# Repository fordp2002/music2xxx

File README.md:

# music2xxx
## Hybrid Music 2000 Clone Midi I/O PCB

This is a hardware clone of the Hybrid Music 2000 Midi add-on for the Acorn BBC Microcomputer model B and Master 128 designed for use with the Hybrid Music 5000 system. It is designed to stack on the Music5xxx clone PCB, and uses the 5V supply from the main board. If used independently of the Music5xxx, you will need to provide a 5V supply - this can come from the BBC Micro's auxiliary power connector.

The Music 2000 Midi interface combined with the AMPLE programming language and the Hybrid Studio 5000 Studio software provides versatile control of external Midi devices. The Music 2000 has 3 Midi output sockets.

Despite having an on-board Midi input port, AMPLE and the Hybrid System cannot use it directly. It is assumed that the Hybrid system is used as a controller and sequencer. However, it is possible to address the interface from user programs.

## The clone

It is designed in Kicad, based upon Colin Fraser's reverse-engineered schematic. http://www.colinfraser.com/m5000/m2000sch.pdf This version uses a different opto-isolator on the Midi input, and implements activity LEDs for the Midi outputs. 

Currently all the 74xx series logic ICs are available new. The 6850 UART ICs are no longer manufactured, but are commonly available second-hand or new-old-stock. 

4/9/19 For standalone use, an optional LM7805 regulator is added to allow powering the board from 9V-12V, as well as an LED to show input activity. A few prototype PCBs have been ordered.

## Using outside the Hybrid system

It's possible to use the m2000 Midi interface in BASIC or machine code - the 6850 Uarts can be read to or written to at addresses: 

* FC08/9 ACIA 1 (MIDI OUT 1)
* FC0A/B ACIA 2 (MIDI OUT 2)
* FC0C/D ACIA 3 (MIDI OUT 3, MIDI IN)

Info from: http://mdfs.net/Info/Comp/BBC/MIDI/m2000

## Resources

* Colin Fraser's Music5000 Resources: http://www.colinfraser.com/m5000/m5000.htm

* The Music2000 Interface User Guide covers all aspects of controlling Midi instruments with AMPLE and Studio 5000. It's available on the retro-kit archive page describing the Hybrid Music 2000: https://www.retro-kit.co.uk/page.cfm/content/Hybrid-Music-2000-Interface/

* A comprehensive archive about the Hybrid Music System: https://www.retro-kit.co.uk/page.cfm/content/Hybrid-Music-5000-Synthesiser/

* Here's the Stardot thread about this project: https://stardot.org.uk/forums/viewtopic.php?f=3&t=16895

* The Stardot 8bit hardware forum often has posts about the Hybrid Music system: https://stardot.org.uk/forums/viewforum.php?f=3

* Information about Midi on the BBC Microcomputer: http://mdfs.net/Info/Comp/BBC/MIDI/

## All BBC MIDI Interfaces

There is a lot of similarity between all BBC Midi Interfaces but also differences. The Data port is always one higher than the the control port.

| Inteface  | OUTS | Out &          | IN &   | INT  |Notes |
| ----------| -----| ---------------| -------| -----| -----| 
| Hybrid 2000 | 3  | 08, 0A, 0C     | 0C     | IRQ  | Has LEDs |
| UMI 4M      | 4  | 80 (00), 88 (08), A8 (28), B0 (30) | 00 (80) | NMI  | Custom 32 Byte ROM @ 38 (B8) |
| POWERTRAN   | 1  | Many 0xFCxx (0xFDxx)    | Choice | IRQ  | Special Output |
| EPE         | 1  | Any            | Any    | None | EPI March 1985 |
| ETI         | 1  | F0, F2         | F0, F2 | IRQ  | ETI 1987 |
| EMR         | 1  | F0             | F0     | IRQ  | 2 Mhz UART Clock (x64) |
| J.G.Harston | 1  | F0             | F0, F2 | IRQ  | |

## Licence

Unless otherwise marked, work in this repository is licenced under [Creative Commons Attribution-ShareAlike 4.0 International License](http://creativecommons.org/licenses/by-sa/4.0/)

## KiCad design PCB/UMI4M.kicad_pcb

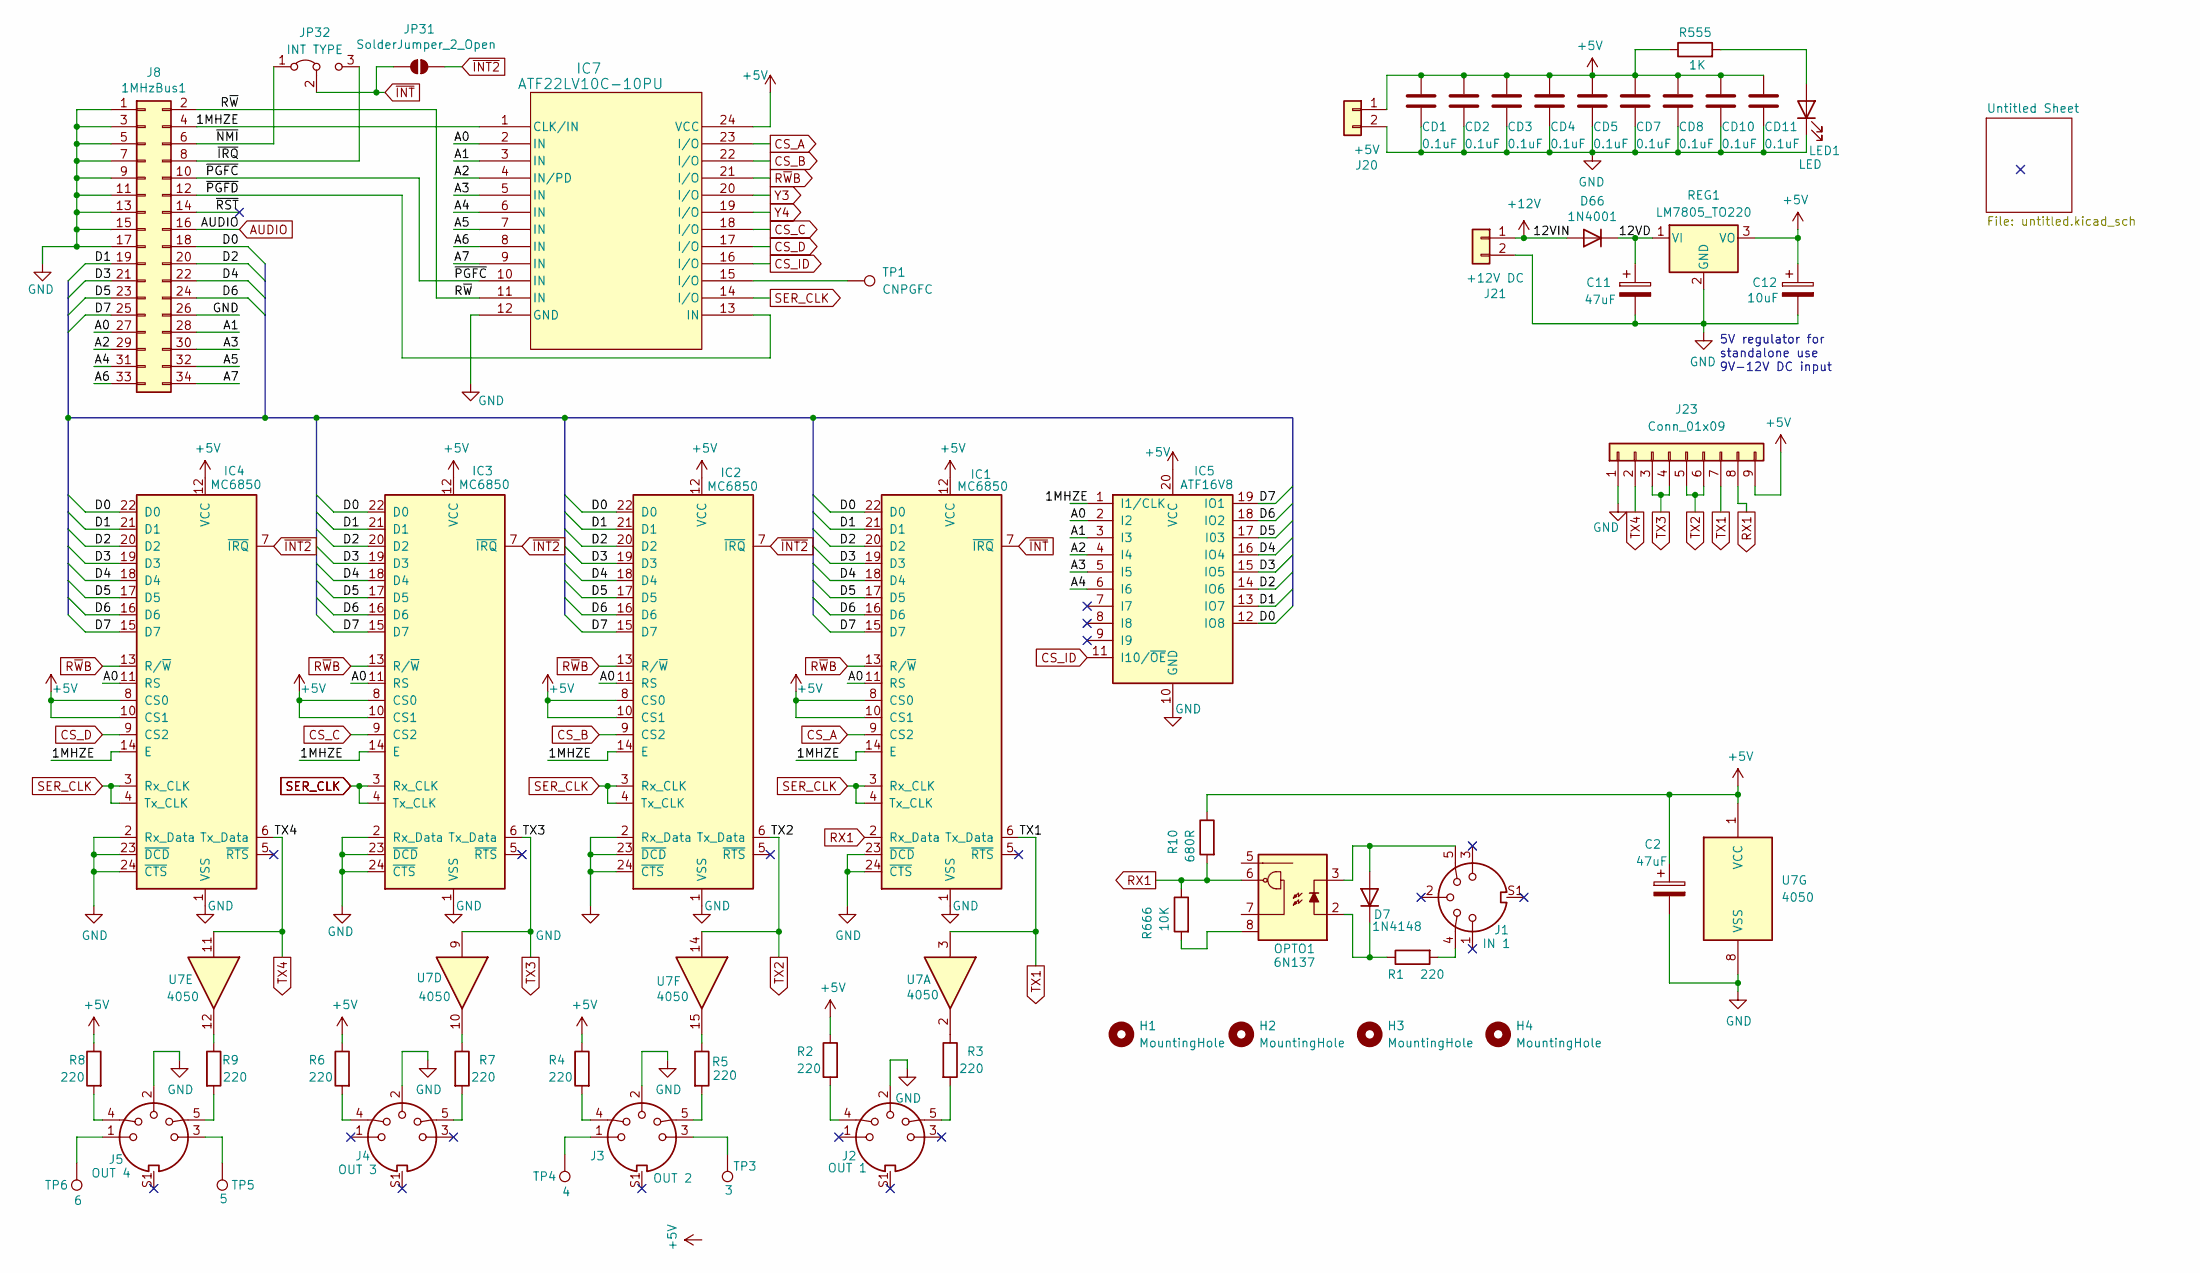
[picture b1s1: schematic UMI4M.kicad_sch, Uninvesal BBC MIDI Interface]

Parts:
C2: 47uF; CP_Radial_D5.0mm_P2.50mm
C11: 47uF; CP_Radial_D5.0mm_P2.00mm
C12: 10uF; CP_Radial_D5.0mm_P2.50mm
CD1, CD2, CD3, CD4, CD5, CD7, CD8, CD10, CD11: 0.1uF; C_Disc_D3.4mm_W2.1mm_P2.54mm
D7: 1N4148; D_DO-35_SOD27_P7.62mm_Horizontal
D66: 1N4001; D_DO-41_SOD81_P10.16mm_Horizontal
H1, H2, H3, H4: MountingHole; MountingHole_4.3mm_M4
IC1, IC2, IC3, IC4: MC6850; DIP-24_W15.24mm_Socket_LongPads
IC5: ATF16V8; DIP-20_W7.62mm_LongPads
IC7: ATF22LV10C-10PU; DIP-24_W7.62mm_Socket_LongPads
J1: IN 1; din_5_pcb_mount_umi
J2: OUT 1; din_5_pcb_mount_umi
J3: OUT 2; din_5_pcb_mount_umi
J4: OUT 3; din_5_pcb_mount_umi
J5: OUT 4; din_5_pcb_mount_umi
J8: 1MHzBus1; IDC-Header_2x17_P2.54mm_Vertical
J20: +5V; TerminalBlock_Phoenix_MKDS-1,5-2-5.08_1x02_P5.08mm_Horizont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
J21: +12V DC; TerminalBlock_Phoenix_MKDS-1,5-2-5.08_1x02_P5.08mm_Horizont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
J23: Conn_01x09; PinHeader_1x09_P2.54mm_Vertical
JP31: SolderJumper_2_Open; SolderJumper-2_P1.3mm_Open_RoundedPad1.0x1.5mm
JP32: INT TYPE; PinHeader_1x03_P2.54mm_Vertical
LED1: LED; LED_D5.0mm
OPTO1: 6N137; DIP-8_W7.62mm_LongPads
R1, R2, R3, R4, R5, R6, R7, R8, R9: 220; R_Axial_DIN0207_L6.3mm_D2.5mm_P10.16mm_Horizontal
R10: 680R; R_Axial_DIN0207_L6.3mm_D2.5mm_P10.16mm_Horizontal
R555: 1K; R_Axial_DIN0207_L6.3mm_D2.5mm_P10.16mm_Horizontal
R666: 10K; R_Axial_DIN0207_L6.3mm_D2.5mm_P10.16mm_Horizontal
REG1: LM7805_TO220; TO-220-3_Vertical
TP1: CNPGFC; TestPoint_THTPad_D2.0mm_Drill1.0mm
TP3: 3; TestPoint_THTPad_D2.0mm_Drill1.0mm
TP4: 4; TestPoint_THTPad_D2.0mm_Drill1.0mm
TP5: 5; TestPoint_THTPad_D2.0mm_Drill1.0mm
TP6: 6; TestPoint_THTPad_D2.0mm_Drill1.0mm
U7: 4050; DIP-16_W7.62mm_LongPads

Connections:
+5V: C2.1, C12.1, CD1.1, CD2.1, CD3.1, CD4.1, CD5.1, CD7.1, CD8.1, CD10.1, CD11.1, IC1.8 (CS0), IC1.10 (CS1), IC1.12 (VCC), IC2.8 (CS0), IC2.10 (CS1), IC2.12 (VCC), IC3.8 (CS0), IC3.10 (CS1), IC3.12 (VCC), IC4.8 (CS0), IC4.10 (CS1), IC4.12 (VCC), IC5.20 (VCC), IC7.24 (VCC), J20.1, J23.9, R2.1, R4.1, R6.1, R8.1, R10.1, R555.1, REG1.3 (VO), U7.1 (VCC); also elsewhere on the board
+12V: D66.2 (A), J21.1
/1MHZE: IC1.14 (E), IC2.14 (E), IC3.14 (E), IC4.14 (E), IC7.1 (CLK/IN), J8.4
/12VD: C11.1, D66.1 (K), REG1.1 (VI)
/A0: IC1.11 (RS), IC2.11 (RS), IC3.11 (RS), IC4.11 (RS), IC5.2 (I2), IC7.2 (IN), J8.27
/A1: IC5.3 (I3), IC7.3 (IN), J8.28
/A2: IC5.4 (I4), IC7.4 (IN/PD), J8.29
/A3: IC5.5 (I5), IC7.5 (IN), J8.30
/A4: IC5.6 (I6), IC7.6 (IN), J8.31
/A5: IC7.7 (IN), J8.32
/A6: IC7.8 (IN), J8.33
/A7: IC7.9 (IN), J8.34
/D0: IC1.22 (D0), IC2.22 (D0), IC3.22 (D0), IC4.22 (D0), IC5.12 (IO8), J8.18
/D1: IC1.21 (D1), IC2.21 (D1), IC3.21 (D1), IC4.21 (D1), IC5.13 (IO7), J8.19
/D2: IC1.20 (D2), IC2.20 (D2), IC3.20 (D2), IC4.20 (D2), IC5.14 (IO6), J8.20
/D3: IC1.19 (D3), IC2.19 (D3), IC3.19 (D3), IC4.19 (D3), IC5.15 (IO5), J8.21
/D4: IC1.18 (D4), IC2.18 (D4), IC3.18 (D4), IC4.18 (D4), IC5.16 (IO4), J8.22
/D5: IC1.17 (D5), IC2.17 (D5), IC3.17 (D5), IC4.17 (D5), IC5.17 (I03), J8.23
/D6: IC1.16 (D6), IC2.16 (D6), IC3.16 (D6), IC4.16 (D6), IC5.18 (IO2), J8.24
/D7: IC1.15 (D7), IC2.15 (D7), IC3.15 (D7), IC4.15 (D7), IC5.19 (IO1), J8.25
/R~W: IC7.11 (IN), J8.2
/~IRQ: J8.8, JP32.3 (B)
/~NMI: J8.6, JP32.1 (A)
/~PGFC: IC7.10 (IN), J8.10
/~PGFD: IC7.13 (IN), J8.12
/~RST: J8.14
AUDIO: J8.16; also elsewhere on the board
CS_A: IC1.9 (CS2), IC7.23 (I/O)
CS_B: IC2.9 (CS2), IC7.22 (I/O)
CS_C: IC3.9 (CS2), IC7.18 (I/O)
CS_D: IC4.9 (CS2), IC7.17 (I/O)
CS_ID: IC5.11 (I10/~OE), IC7.16 (I/O)
GND: C2.2, C11.2, C12.2, CD1.2, CD2.2, CD3.2, CD4.2, CD5.2, CD7.2, CD8.2, CD10.2, CD11.2, IC1.1 (VSS), IC1.23 (~DCD), IC1.24 (~CTS), IC2.1 (VSS), IC2.2 (Rx_Data), IC2.23 (~DCD), IC2.24 (~CTS), IC3.1 (VSS), IC3.2 (Rx_Data), IC3.23 (~DCD), IC3.24 (~CTS), IC4.1 (VSS), IC4.2 (Rx_Data), IC4.23 (~DCD), IC4.24 (~CTS), IC5.10 (GND), IC7.12 (GND), J2.2, J3.2, J4.2, J5.2, J8.1, J8.3, J8.5, J8.7, J8.9, J8.11, J8.13, J8.15, J8.17, J8.26, J20.2, J21.2, J23.1, LED1.1 (K), REG1.2 (GND), U7.8 (VSS); also elsewhere on the board
unnamed: D7.2 (A), J1.5, OPTO1.3
unnamed: D7.1 (K), OPTO1.2, R1.1
unnamed: IC7.15 (I/O), TP1.1
unnamed: J1.4, R1.2
unnamed: J2.4, R2.2
unnamed: J2.5, R3.2
unnamed: J3.1, TP4.1
unnamed: J3.3, TP3.1
unnamed: J3.4, R4.2
unnamed: J3.5, R5.2
unnamed: J4.4, R6.2
unnamed: J4.5, R7.2
unnamed: J5.1, TP6.1
unnamed: J5.3, TP5.1
unnamed: J5.4, R8.2
unnamed: J5.5, R9.2
unnamed: LED1.2 (A), R555.2
unnamed: OPTO1.8, R666.2
unnamed: R3.1, U7.2
unnamed: R5.1, U7.15
unnamed: R7.1, U7.10
unnamed: R9.1, U7.12
RX1: IC1.2 (Rx_Data), J23.8, OPTO1.6, R10.2, R666.1
R~WB: IC1.13 (R/~W), IC2.13 (R/~W), IC3.13 (R/~W), IC4.13 (R/~W), IC7.21 (I/O)
SER_CLK: IC1.3 (Rx_CLK), IC1.4 (Tx_CLK), IC2.3 (Rx_CLK), IC2.4 (Tx_CLK), IC3.3 (Rx_CLK), IC3.4 (Tx_CLK), IC4.3 (Rx_CLK), IC4.4 (Tx_CLK), IC7.14 (I/O)
TX1: IC1.6 (Tx_Data), J23.7, U7.3
TX2: IC2.6 (Tx_Data), J23.5, J23.6, U7.14
TX3: IC3.6 (Tx_Data), J23.3, J23.4, U7.9
TX4: IC4.6 (Tx_Data), J23.2, U7.11
Y3: IC7.20 (I/O); also elsewhere on the board
Y4: IC7.19 (I/O); also elsewhere on the board
~INT2: IC2.7 (~IRQ), IC3.7 (~IRQ), IC4.7 (~IRQ), JP31.2 (B)
~INT: IC1.7 (~IRQ), JP31.1 (A), JP32.2 (C)

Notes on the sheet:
5V regulator for standalone use 9V-12V DC input

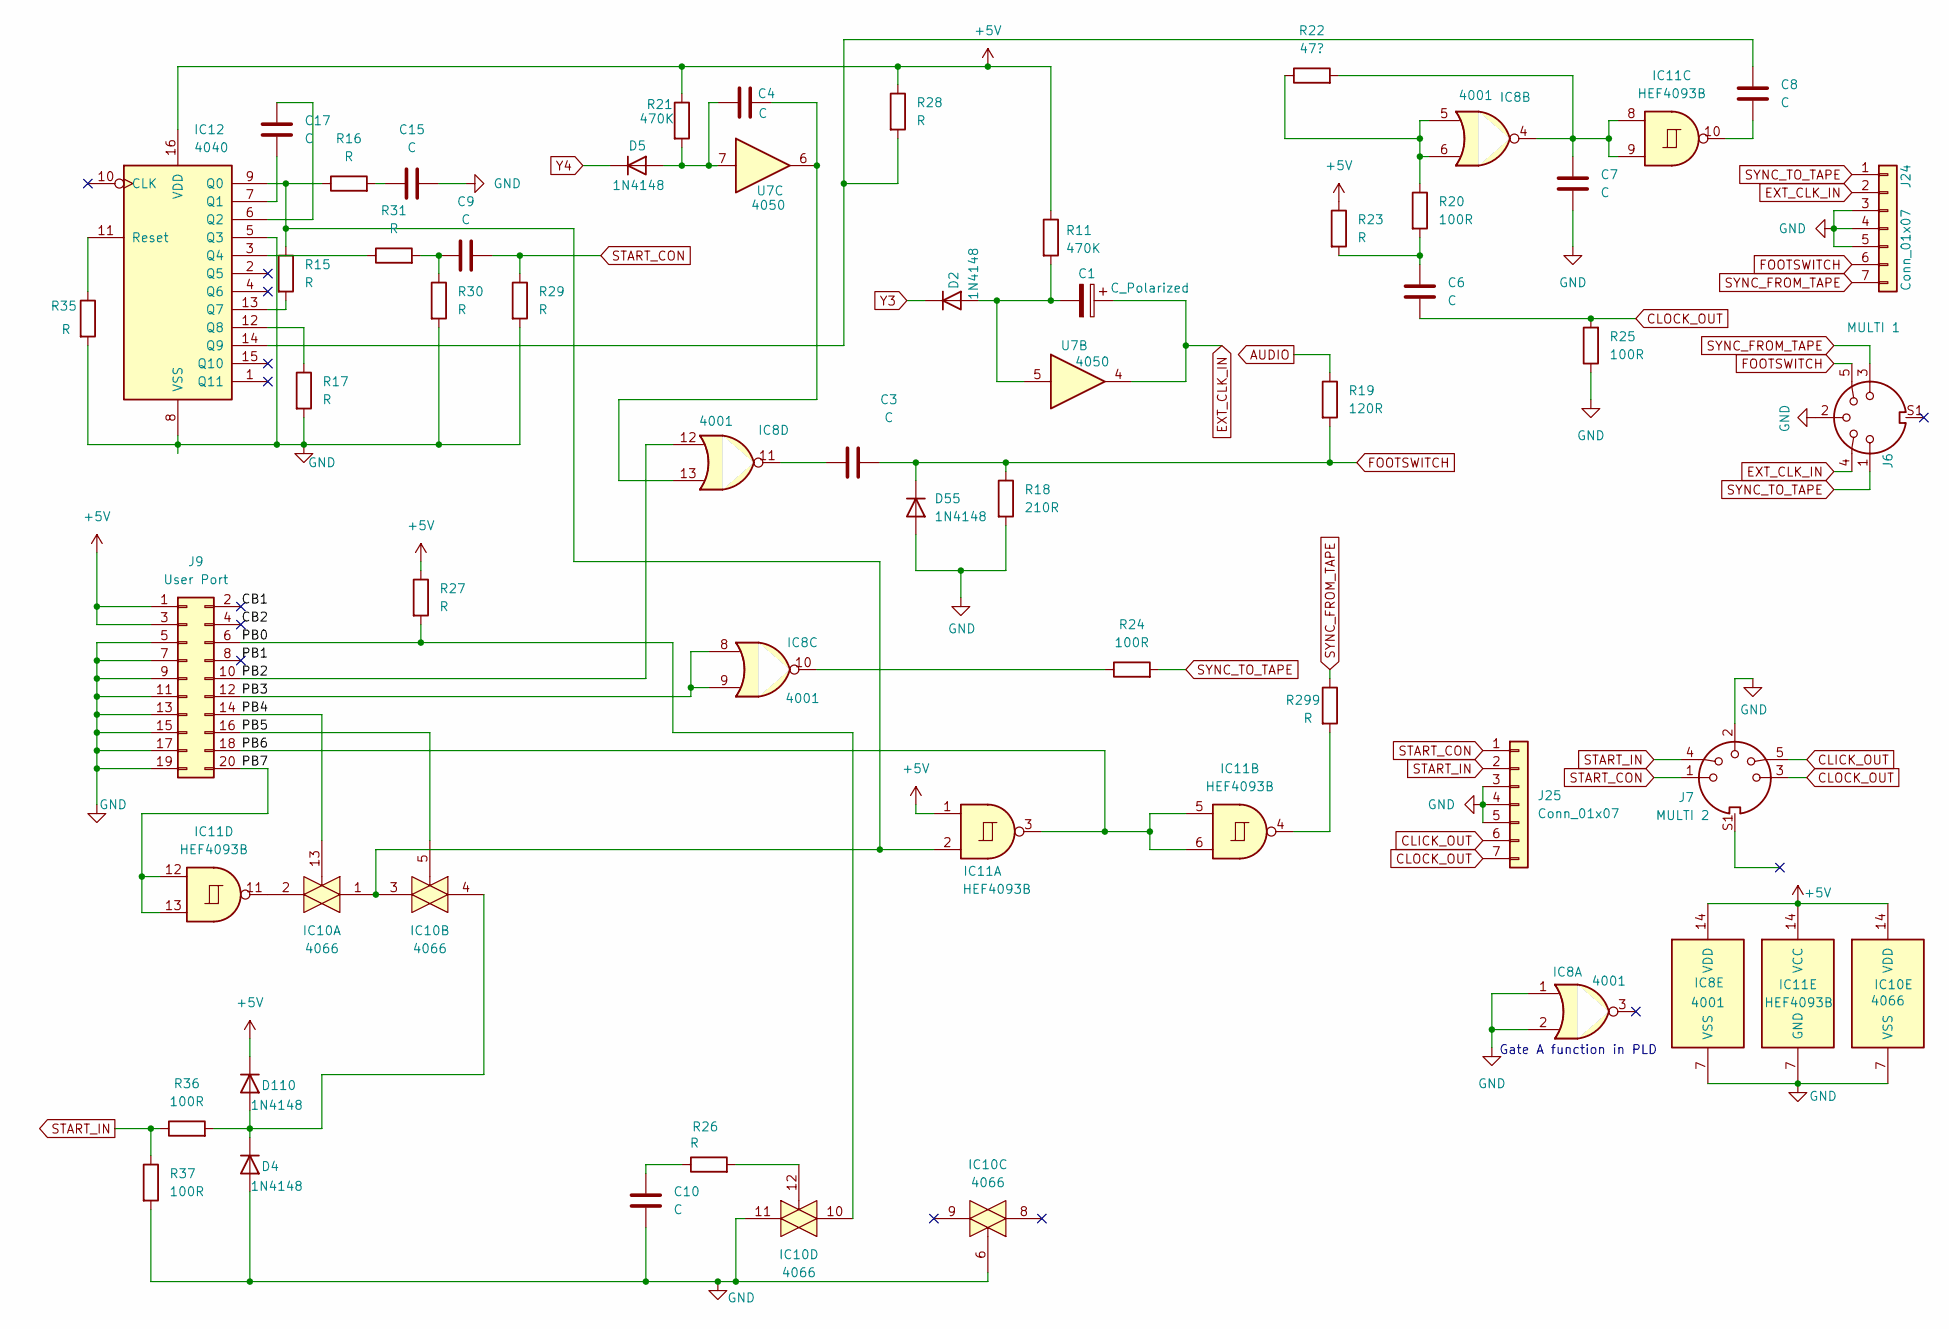
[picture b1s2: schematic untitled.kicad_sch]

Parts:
C1: C_Polarized; CP_Radial_Tantal_D4.5mm_P2.50mm
C3, C4, C8, C9, C10: C; C_Disc_D7.5mm_W2.5mm_P5.00mm
C6, C7, C15, C17: C; C_Disc_D3.4mm_W2.1mm_P2.50mm
D2, D4, D5, D55, D110: 1N4148; D_DO-35_SOD27_P7.62mm_Horizontal
IC8: 4001; DIP-14_W7.62mm_Socket_LongPads
IC10: 4066; DIP-14_W7.62mm_Socket_LongPads
IC11: HEF4093B; DIP-14_W7.62mm_Socket_LongPads
IC12: 4040; DIP-16_W7.62mm_Socket_LongPads
J6: MULTI 1; din_5_pcb_mount_umi
J7: MULTI 2; din_5_pcb_mount_umi
J9: User Port; IDC-Header_2x10_P2.54mm_Vertical
J24, J25: Conn_01x07; PinHeader_1x07_P2.54mm_Vertical
R11, R21: 470K; R_Axial_DIN0207_L6.3mm_D2.5mm_P10.16mm_Horizontal
R15, R16, R17, R23, R26, R27, R28, R29, R30, R31, R35, R299: R; R_Axial_DIN0207_L6.3mm_D2.5mm_P10.16mm_Horizontal
R18: 210R; R_Axial_DIN0207_L6.3mm_D2.5mm_P10.16mm_Horizontal
R19: 120R; R_Axial_DIN0207_L6.3mm_D2.5mm_P10.16mm_Horizontal
R20, R24, R25, R36, R37: 100R; R_Axial_DIN0207_L6.3mm_D2.5mm_P10.16mm_Horizontal
R22: 47?; R_Axial_DIN0207_L6.3mm_D2.5mm_P10.16mm_Horizontal
U7: 4050; DIP-16_W7.62mm_LongPads

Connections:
+5V: D110.1 (K), IC8.14 (VDD), IC10.14 (VDD), IC11.1, IC11.14 (VCC), IC12.16 (VDD), J9.1, J9.3, R11.1, R21.1, R23.1, R27.1, R28.1; also elsewhere on the board
/Untitled Sheet/CB1: J9.2
/Untitled Sheet/CB2: J9.4
/Untitled Sheet/PB0: IC10.10, J9.6, R27.2
/Untitled Sheet/PB1: J9.8
/Untitled Sheet/PB2: IC8.12, J9.10
/Untitled Sheet/PB3: IC8.8, IC8.9, J9.12
/Untitled Sheet/PB4: IC10.13, J9.14
/Untitled Sheet/PB5: IC10.5, J9.16
/Untitled Sheet/PB6: IC11.3, IC11.5, IC11.6, J9.18
/Untitled Sheet/PB7: IC11.12, IC11.13, J9.20
AUDIO: R19.1; also elsewhere on the board
CLICK_OUT: J7.5, J25.6
CLOCK_OUT: C6.2, J7.3, J25.7, R25.2
EXT_CLK_IN: C1.1, J6.4, J24.2, U7.4
FOOTSWITCH: C3.2, D55.1 (K), J6.5, J24.6, R18.1, R19.2
GND: C7.2, C10.2, C15.2, D4.2 (A), D55.2 (A), IC8.1, IC8.2, IC8.7 (VSS), IC10.6, IC10.7 (VSS), IC10.11, IC11.7 (GND), IC12.5 (Q3), IC12.8 (VSS), J6.2, J7.2, J9.5, J9.7, J9.9, J9.11, J9.13, J9.15, J9.17, J9.19, J24.3, J24.4, J24.5, J25.3, J25.4, J25.5, R17.2, R18.2, R25.1, R29.2, R30.2, R35.2, R37.2; also elsewhere on the board
unnamed: C3.1, IC8.11
unnamed: C4.1, IC8.13, U7.6
unnamed: C6.1, R20.2, R23.2
unnamed: C7.1, IC8.4, IC11.8, IC11.9, R22.2
unnamed: C8.2, IC11.10
unnamed: C9.1, R30.1, R31.2
unnamed: C10.1, R26.1
unnamed: C15.1, R16.2
unnamed: C1.2, D2.2 (A), R11.2, U7.5
unnamed: C4.2, D5.2 (A), R21.2, U7.7
unnamed: D4.1 (K), D110.2 (A), IC10.4, R36.2
unnamed: IC8.5, IC8.6, R20.1, R22.1
unnamed: IC8.10, R24.1
unnamed: IC10.2, IC11.11
unnamed: IC10.12, R26.2
unnamed: IC11.4, R299.2
unnamed: IC10.1, IC10.3, IC11.2, IC12.9 (Q0), R15.1, R16.1
unnamed: C17.2, IC12.7 (Q1)
unnamed: C17.1, IC12.6 (Q2)
unnamed: IC12.3 (Q4), R31.1
unnamed: IC12.13 (Q7), R15.2
unnamed: IC12.12 (Q8), R17.1
unnamed: C8.1, IC12.14 (Q9), R28.2
unnamed: IC12.11 (Reset), R35.1
START_CON: C9.2, J7.1, J25.1, R29.1
START_IN: J7.4, J25.2, R36.1, R37.1
SYNC_FROM_TAPE: J6.3, J24.7, R299.1
SYNC_TO_TAPE: J6.1, J24.1, R24.2
Y3: D2.1 (K); also elsewhere on the board
Y4: D5.1 (K); also elsewhere on the board

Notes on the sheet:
Gate A function in PLD

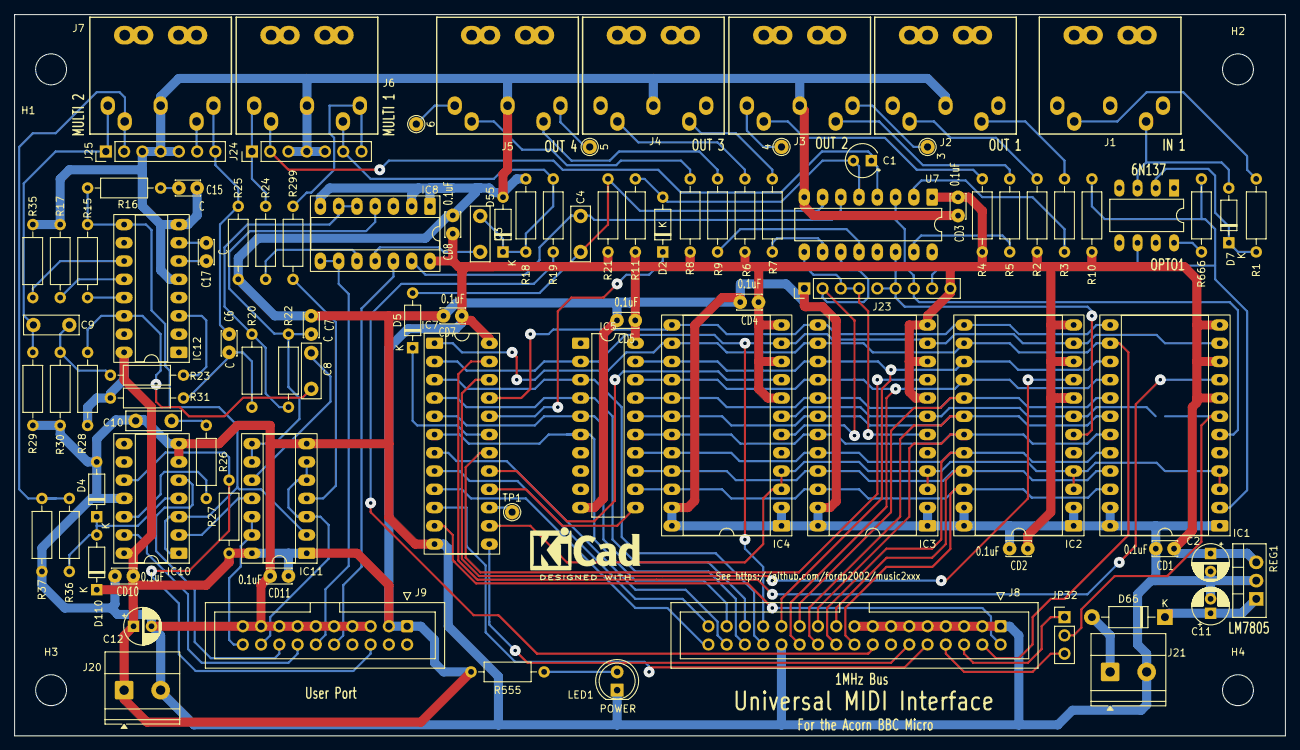
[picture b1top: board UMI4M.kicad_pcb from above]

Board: 2 copper layers, 176.8 x 100.3 mm, 102 parts (1 on the bottom side), 104 nets.

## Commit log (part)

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2025-03-03 WIP Universal MIDI Interface
